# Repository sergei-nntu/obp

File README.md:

# Open Battery Pack (OBP-1)

Arduino-based open-source hardware power bank for DIY and Robotic applications. This repository contains the schematics, Arduino firmware, python library for connection from the computer and FreeCAD case design files. 

# Installing Arduino code
Arduino source code is located in folder `src/arduino/OpenBatteryPack`. Open it with Arduino IDE and flash it into your Arduino board.

# Python library example
Flash the Arduino firmware into your board. Make sure it is connected through USB. Then run the example:

`cd src/python`

`python3 example.py`

# Technical Documentation
The architecture documentation can be found in `doc` folder.

# Case 3D Printing
STL files for 3d printing can be found in `case` folder.

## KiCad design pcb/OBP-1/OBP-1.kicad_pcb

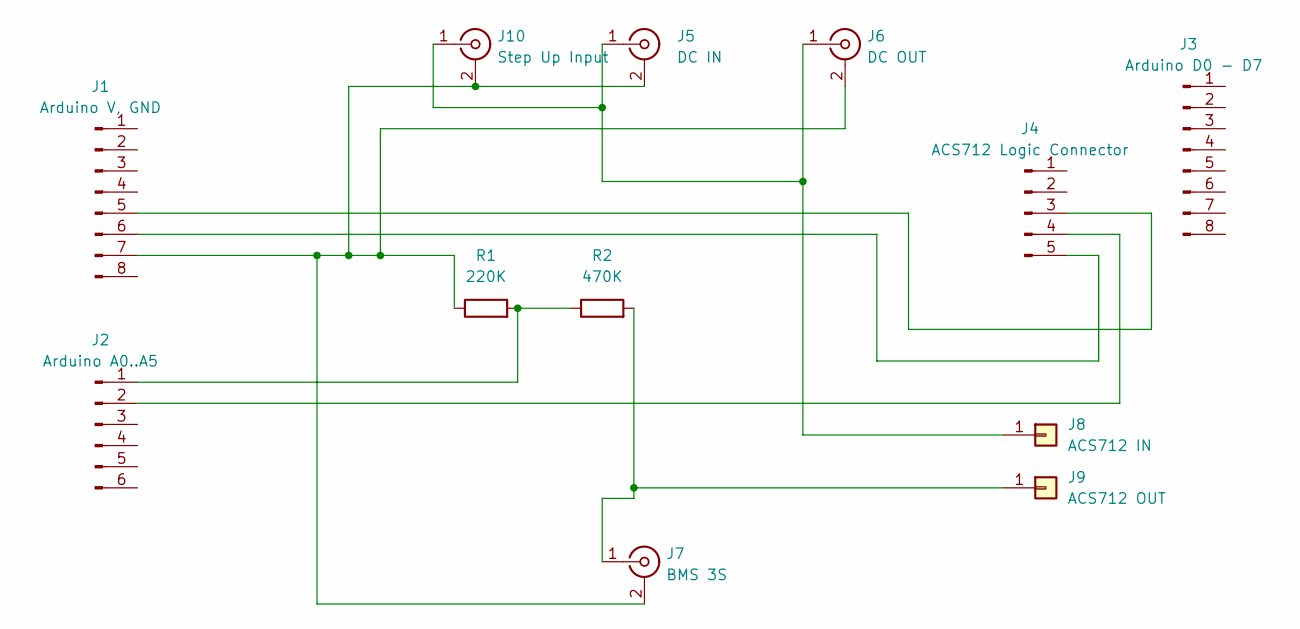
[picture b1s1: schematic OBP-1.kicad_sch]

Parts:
J1: Arduino V, GND; PinHeader_1x08_P2.54mm_Vertical
J2: Arduino A0..A5; PinHeader_1x06_P2.54mm_Vertical
J3: Arduino D0 - D7; PinHeader_1x08_P2.54mm_Vertical
J4: ACS712 Logic Connector; PinHeader_1x05_P2.54mm_Vertical
J5: DC IN; SolderWire-0.1sqmm_1x02_P3.6mm_D0.4mm_OD1mm
J6: DC OUT; SolderWire-0.1sqmm_1x02_P3.6mm_D0.4mm_OD1mm
J7: BMS 3S; SolderWire-0.1sqmm_1x02_P3.6mm_D0.4mm_OD1mm
J8: ACS712 IN; SolderWire-0.1sqmm_1x01_D0.4mm_OD1mm
J9: ACS712 OUT; SolderWire-0.1sqmm_1x01_D0.4mm_OD1mm
J10: Step Up Input; SolderWire-0.1sqmm_1x02_P3.6mm_D0.4mm_OD1mm
R1: 220K; R_Axial_DIN0207_L6.3mm_D2.5mm_P10.16mm_Horizontal
R2: 470K; R_Axial_DIN0207_L6.3mm_D2.5mm_P10.16mm_Horizontal

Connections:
unnamed: J1.5, J4.3
unnamed: J1.6, J4.5
unnamed: J1.7, J5.2 (Ext), J6.2 (Ext), J7.2 (Ext), J10.2 (Ext), R1.1
unnamed: J2.1, R1.2, R2.1
unnamed: J2.2, J4.4
unnamed: J5.1 (In), J6.1 (In), J8.1, J10.1 (In)
unnamed: J7.1 (In), J9.1, R2.2

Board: 2 copper layers, 12 parts (0 on the bottom side), 7 nets, no tracks yet.

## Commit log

2023-02-10 Initial Version. Added README and LICENSE files. Added FreeCad model for the OBP-1 case
2023-02-16 Added OSP source code
2023-02-16 Open Battery Pack Arduino Firmware Added
2023-02-17 OBP-1. First version of schematics and PCB for main board added
2023-02-17 Added OBP-1 Python Library Example
2023-02-17 Added STL files for OBP-1 Case and Cover
2023-02-18 Error in FSM states definition fixed. Architecture doc added
2023-02-20 Architecture Doc updated. v0.3.0. Added the SOC estimation algorithm description
2023-02-20 OBP Images Added
